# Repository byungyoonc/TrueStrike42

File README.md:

# TrueStrike42

TrueStrike42 is a columnar staggered unibody split Hall-effect keyboard designed to maximize performance[^1] and minimize finger fatigue.

[^1]: specifically on rhythm games

# Layout

# How to build
Refer to the [build guide](doc/buildguide.md) for detailed instructions.

# Firmware
> [!WARNING]
> MCU will behave very erratic (e.g. sending random keypresses rapidly) right after flashing the firmware, before soldering all the components on the board. This is because MCU's analogue pins are connected to nothing, resulting in noise sensor values. 
>
> Disconnect the MCU from the PC as soon as possible after the successful firmware flash to prevent chaos.
> 
## Use Precompiled Binary
Flash `fw/truestrike42_via.uf2` to your RP2040 microcontroller in bootloader mode.

## Build on Your Own
### Option A
Copy the `fw/truestrike42` folder into your cloned QMK Firmware repository's `keyboards` folder, then run `qmk compile -kb truestrike42 -km via`.

### Option B
- [QMK Firmware fork](https://github.com/byungyoonc/qmk_firmware/tree/Truestrike42)
- [VIA QMK Userspace fork](https://github.com/byungyoonc/qmk_userspace_via/tree/truestrike42)

The branches above are from my fork of the QMK Firmware/Userspace repository which supports firmware compilation for TrueStrike42. 

Follow [this guide for External QMK Userspace](https://docs.qmk.fm/newbs_external_userspace) to build it yourself.

# Using VIA HE Configurations
You can access the following tools in VIA by selecting **HE TOOLS** in the menu next to **LIGHTING**.

## Load VIA Definition
Open `fw/truestrike42.json` in VIA's **DESIGN** tab to enable VIA support for TrueStrike42.

## Calibrations
**Make sure to run the calibration at least once before using the keyboard!**
### Bottoming Calibration
Calibrates Hall-effect sensor values for each switch when it is fully bottomed out.

Toggle on, fully bottom out each switch, then toggle off.

### Noise Floor Calibration
Calibrates the ambient magnetic flux fluctuation detected by the Hall-effect sensors.

Click once while leaving the keyboard untouched for a brief period. The firmware samples the noise baseline.

### Show Calibration Data
Prints out current calibration data to the debug console.

### Clear Bottoming Calibration Data
Resets Bottoming Calibration Data to prepare for recalibration. Use this when replacing your Hall-effect switches.

## Actuation
### Mode
Choose between APC and Rapid Trigger.

APC works like a traditional digital switch, but you can change where actuation/release occurs.

Rapid Trigger tracks the switch's height to determine whether the key is being pressed down or released.

### Offsets
Sets the offset values for the selected Mode.

The value ranges from 1 (Topmost) to 255 (Bottommost).

# Related Projects

- [Cipulot's EC Boards](https://github.com/qmk/qmk_firmware/tree/master/keyboards/cipulot/common)
  - TrueStrike42's QMK firmware code for analog signal processing was heavily based on the code for the Cipulot's EC boards.
- [Boardloaf HE](https://github.com/Hanthebot/Boardloaf-HE)
  - 36 key HE split keyboard project by Hanthebot. Their schematics design was derived from TrueStrike42.

# Copyright Notice
`True-Strike-icon.kicad_mod` was created by modifying an icon image for True Strike in the game Baldur's Gate 3, a game by Larian Studios. I used it in accordance with the [Larian Fan Content Policy](https://larian.com/fan-content-policy).

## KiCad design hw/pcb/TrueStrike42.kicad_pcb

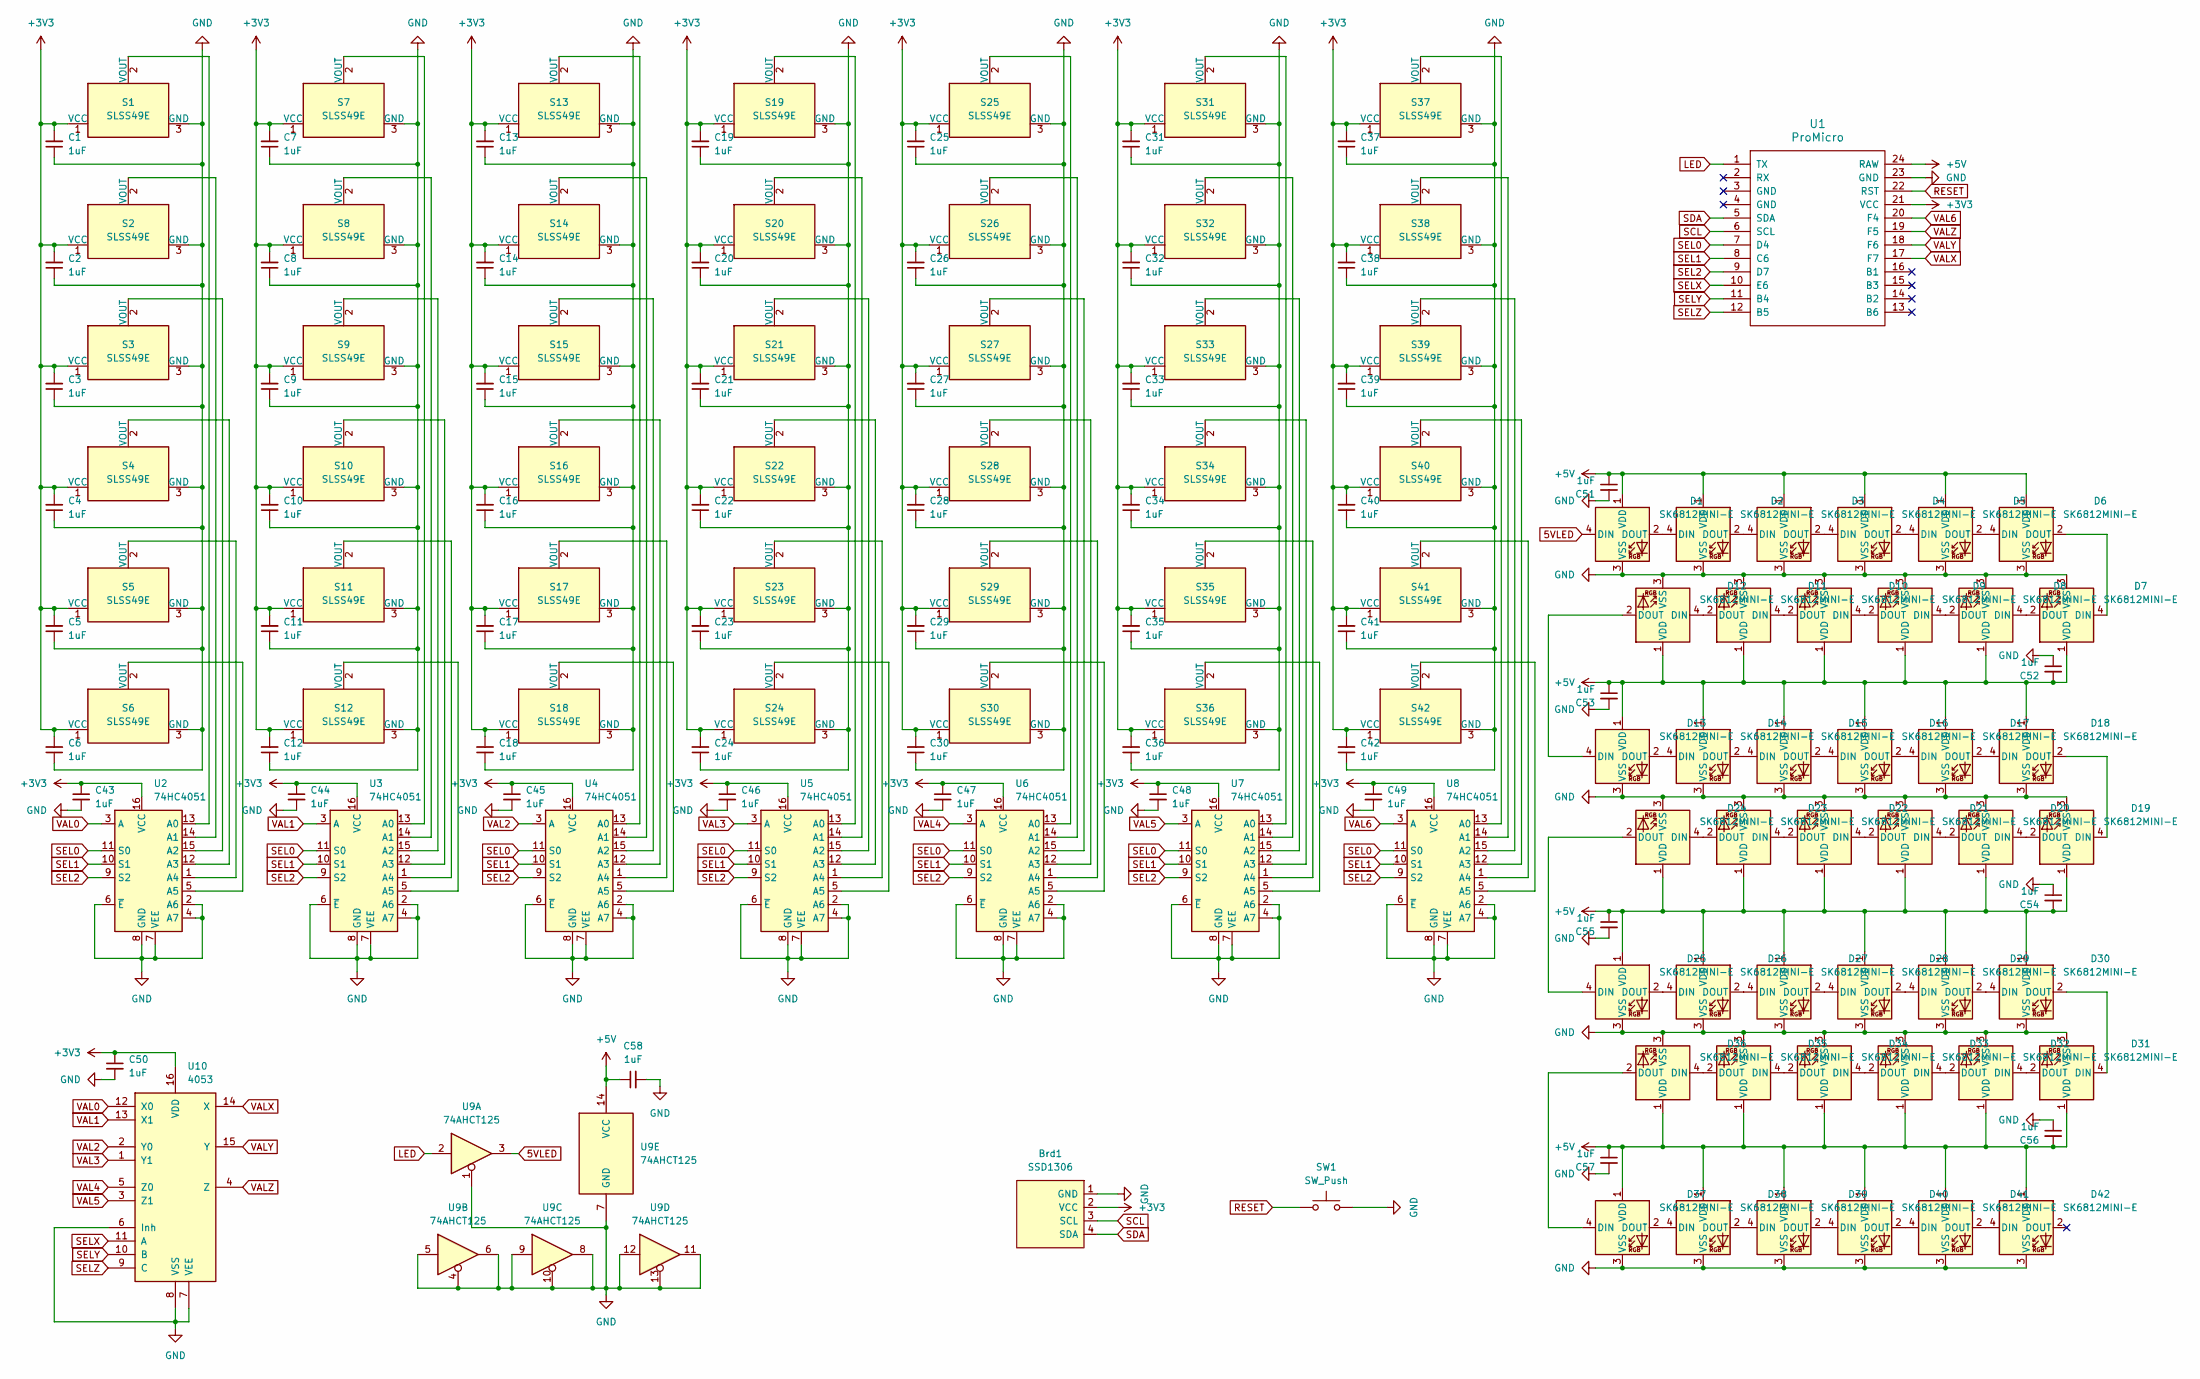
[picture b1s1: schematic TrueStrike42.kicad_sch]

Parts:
Brd1: SSD1306; 128x64OLED
C1, C2, C3, C4, C5, C6, C7, C8, C9, C10, C11, C12, C13, C14, C15, C16, C17, C18, C19, C20, C21, C22, C23, C24, C25, C26, C27, C28, C29, C30, C31, C32, C33, C34, C35, C36, C37, C38, C39, C40, C41, C42, C43, C44, C45, C46, C47, C48, C49, C50, C51, C52, C53, C54, C55, C56, C57, C58: 1uF; C_0805_2012Metric_Pad1.18x1.45mm_HandSolder
D1, D2, D3, D4, D5, D6, D13, D14, D15, D16, D17, D18, D25, D26, D27, D28, D29, D30, D37, D38, D39, D40, D41, D42: SK6812MINI-E; SK6812MINI-E_nusumi
D7, D8, D9, D10, D11, D12, D19, D20, D21, D22, D23, D24, D31, D32, D33, D34, D35, D36: SK6812MINI-E; SK6812MINI-E_nusumi_Rotated
S1, S2, S3, S4, S5, S6, S7, S8, S9, S10, S11, S12, S13, S14, S15, S16, S17, S18, S19, S20, S21, S22, S23, S24, S25, S26, S27, S28, S29, S30, S31, S32, S33, S34, S35, S36, S37, S38, S41, S42: SLSS49E; HE-Switch-1U
S39, S40: SLSS49E; HE-Switch-2U
SW1: SW_Push; SW_Tactile_SPST_NO_Straight_CK_PTS636Sx25SMTRLFS
U1: ProMicro
U2, U3, U4, U5, U6, U7, U8: 74HC4051; SOIC-16_3.9x9.9mm_P1.27mm
U9: 74AHCT125; SOIC-14_3.9x8.7mm_P1.27mm
U10: 4053; SOIC-16_3.9x9.9mm_P1.27mm

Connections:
5VLED: D1.4 (DIN), U9.3
+3V3: Brd1.2 (VCC), C1.2, C2.2, C3.2, C4.2, C5.2, C6.2, C7.2, C8.2, C9.2, C10.2, C11.2, C12.2, C13.2, C14.2, C15.2, C16.2, C17.2, C18.2, C19.2, C20.2, C21.2, C22.2, C23.2, C24.2, C25.2, C26.2, C27.2, C28.2, C29.2, C30.2, C31.2, C32.2, C33.2, C34.2, C35.2, C36.2, C37.2, C38.2, C39.2, C40.2, C41.2, C42.2, C43.1, C44.1, C45.1, C46.1, C47.1, C48.1, C49.1, C50.1, S1.1 (VCC), S2.1 (VCC), S3.1 (VCC), S4.1 (VCC), S5.1 (VCC), S6.1 (VCC), S7.1 (VCC), S8.1 (VCC), S9.1 (VCC), S10.1 (VCC), S11.1 (VCC), S12.1 (VCC), S13.1 (VCC), S14.1 (VCC), S15.1 (VCC), S16.1 (VCC), S17.1 (VCC), S18.1 (VCC), S19.1 (VCC), S20.1 (VCC), S21.1 (VCC), S22.1 (VCC), S23.1 (VCC), S24.1 (VCC), S25.1 (VCC), S26.1 (VCC), S27.1 (VCC), S28.1 (VCC), S29.1 (VCC), S30.1 (VCC), S31.1 (VCC), S32.1 (VCC), S33.1 (VCC), S34.1 (VCC), S35.1 (VCC), S36.1 (VCC), S37.1 (VCC), S38.1 (VCC), S39.1 (VCC), S40.1 (VCC), S41.1 (VCC), S42.1 (VCC), U1.21 (VCC), U2.16 (VCC), U3.16 (VCC), U4.16 (VCC), U5.16 (VCC), U6.16 (VCC), U7.16 (VCC), U8.16 (VCC), U10.16 (VDD)
+5V: C51.1, C52.2, C53.1, C54.2, C55.1, C56.2, C57.1, C58.1, D1.1 (VDD), D2.1 (VDD), D3.1 (VDD), D4.1 (VDD), D5.1 (VDD), D6.1 (VDD), D7.1 (VDD), D8.1 (VDD), D9.1 (VDD), D10.1 (VDD), D11.1 (VDD), D12.1 (VDD), D13.1 (VDD), D14.1 (VDD), D15.1 (VDD), D16.1 (VDD), D17.1 (VDD), D18.1 (VDD), D19.1 (VDD), D20.1 (VDD), D21.1 (VDD), D22.1 (VDD), D23.1 (VDD), D24.1 (VDD), D25.1 (VDD), D26.1 (VDD), D27.1 (VDD), D28.1 (VDD), D29.1 (VDD), D30.1 (VDD), D31.1 (VDD), D32.1 (VDD), D33.1 (VDD), D34.1 (VDD), D35.1 (VDD), D36.1 (VDD), D37.1 (VDD), D38.1 (VDD), D39.1 (VDD), D40.1 (VDD), D41.1 (VDD), D42.1 (VDD), U1.24 (RAW), U9.14 (VCC)
GND: Brd1.1 (GND), C1.1, C2.1, C3.1, C4.1, C5.1, C6.1, C7.1, C8.1, C9.1, C10.1, C11.1, C12.1, C13.1, C14.1, C15.1, C16.1, C17.1, C18.1, C19.1, C20.1, C21.1, C22.1, C23.1, C24.1, C25.1, C26.1, C27.1, C28.1, C29.1, C30.1, C31.1, C32.1, C33.1, C34.1, C35.1, C36.1, C37.1, C38.1, C39.1, C40.1, C41.1, C42.1, C43.2, C44.2, C45.2, C46.2, C47.2, C48.2, C49.2, C50.2, C51.2, C52.1, C53.2, C54.1, C55.2, C56.1, C57.2, C58.2, D1.3 (VSS), D2.3 (VSS), D3.3 (VSS), D4.3 (VSS), D5.3 (VSS), D6.3 (VSS), D7.3 (VSS), D8.3 (VSS), D9.3 (VSS), D10.3 (VSS), D11.3 (VSS), D12.3 (VSS), D13.3 (VSS), D14.3 (VSS), D15.3 (VSS), D16.3 (VSS), D17.3 (VSS), D18.3 (VSS), D19.3 (VSS), D20.3 (VSS), D21.3 (VSS), D22.3 (VSS), D23.3 (VSS), D24.3 (VSS), D25.3 (VSS), D26.3 (VSS), D27.3 (VSS), D28.3 (VSS), D29.3 (VSS), D30.3 (VSS), D31.3 (VSS), D32.3 (VSS), D33.3 (VSS), D34.3 (VSS), D35.3 (VSS), D36.3 (VSS), D37.3 (VSS), D38.3 (VSS), D39.3 (VSS), D40.3 (VSS), D41.3 (VSS), D42.3 (VSS), S1.3 (GND), S2.3 (GND), S3.3 (GND), S4.3 (GND), S5.3 (GND), S6.3 (GND), S7.3 (GND), S8.3 (GND), S9.3 (GND), S10.3 (GND), S11.3 (GND), S12.3 (GND), S13.3 (GND), S14.3 (GND), S15.3 (GND), S16.3 (GND), S17.3 (GND), S18.3 (GND), S19.3 (GND), S20.3 (GND), S21.3 (GND), S22.3 (GND), S23.3 (GND), S24.3 (GND), S25.3 (GND), S26.3 (GND), S27.3 (GND), S28.3 (GND), S29.3 (GND), S30.3 (GND), S31.3 (GND), S32.3 (GND), S33.3 (GND), S34.3 (GND), S35.3 (GND), S36.3 (GND), S37.3 (GND), S38.3 (GND), S39.3 (GND), S40.3 (GND), S41.3 (GND), S42.3 (GND), SW1.2, U1.23 (GND), U2.2 (A6), U2.4 (A7), U2.6 (~E), U2.7 (VEE), U2.8 (GND), U3.2 (A6), U3.4 (A7), U3.6 (~E), U3.7 (VEE), U3.8 (GND), U4.2 (A6), U4.4 (A7), U4.6 (~E), U4.7 (VEE), U4.8 (GND), U5.2 (A6), U5.4 (A7), U5.6 (~E), U5.7 (VEE), U5.8 (GND), U6.2 (A6), U6.4 (A7), U6.6 (~E), U6.7 (VEE), U6.8 (GND), U7.2 (A6), U7.4 (A7), U7.6 (~E), U7.7 (VEE), U7.8 (GND), U8.2 (A6), U8.4 (A7), U8.6 (~E), U8.7 (VEE), U8.8 (GND), U9.1, U9.4, U9.5, U9.6, U9.7 (GND), U9.8, U9.9, U9.10, U9.11, U9.12, U9.13, U10.6 (Inh), U10.7 (VEE), U10.8 (VSS); also elsewhere on the board
LED: U1.1 (TX), U9.2
unnamed: D1.2 (DOUT), D2.4 (DIN)
unnamed: D2.2 (DOUT), D3.4 (DIN)
unnamed: D3.2 (DOUT), D4.4 (DIN)
unnamed: D4.2 (DOUT), D5.4 (DIN)
unnamed: D5.2 (DOUT), D6.4 (DIN)
unnamed: D6.2 (DOUT), D7.4 (DIN)
unnamed: D7.2 (DOUT), D8.4 (DIN)
unnamed: D8.2 (DOUT), D9.4 (DIN)
unnamed: D9.2 (DOUT), D10.4 (DIN)
unnamed: D10.2 (DOUT), D11.4 (DIN)
unnamed: D11.2 (DOUT), D12.4 (DIN)
unnamed: D12.2 (DOUT), D13.4 (DIN)
unnamed: D13.2 (DOUT), D14.4 (DIN)
unnamed: D14.2 (DOUT), D15.4 (DIN)
unnamed: D15.2 (DOUT), D16.4 (DIN)
unnamed: D16.2 (DOUT), D17.4 (DIN)
unnamed: D17.2 (DOUT), D18.4 (DIN)
unnamed: D18.2 (DOUT), D19.4 (DIN)
unnamed: D19.2 (DOUT), D20.4 (DIN)
unnamed: D20.2 (DOUT), D21.4 (DIN)
unnamed: D21.2 (DOUT), D22.4 (DIN)
unnamed: D22.2 (DOUT), D23.4 (DIN)
unnamed: D23.2 (DOUT), D24.4 (DIN)
unnamed: D24.2 (DOUT), D25.4 (DIN)
unnamed: D25.2 (DOUT), D26.4 (DIN)
unnamed: D26.2 (DOUT), D27.4 (DIN)
unnamed: D27.2 (DOUT), D28.4 (DIN)
unnamed: D28.2 (DOUT), D29.4 (DIN)
unnamed: D29.2 (DOUT), D30.4 (DIN)
unnamed: D30.2 (DOUT), D31.4 (DIN)
unnamed: D31.2 (DOUT), D32.4 (DIN)
unnamed: D32.2 (DOUT), D33.4 (DIN)
unnamed: D33.2 (DOUT), D34.4 (DIN)
unnamed: D34.2 (DOUT), D35.4 (DIN)
unnamed: D35.2 (DOUT), D36.4 (DIN)
unnamed: D36.2 (DOUT), D37.4 (DIN)
unnamed: D37.2 (DOUT), D38.4 (DIN)
unnamed: D38.2 (DOUT), D39.4 (DIN)
unnamed: D39.2 (DOUT), D40.4 (DIN)
unnamed: D40.2 (DOUT), D41.4 (DIN)
unnamed: D41.2 (DOUT), D42.4 (DIN)
unnamed: S1.2 (VOUT), U2.13 (A0)
unnamed: S2.2 (VOUT), U2.14 (A1)
unnamed: S3.2 (VOUT), U2.15 (A2)
unnamed: S4.2 (VOUT), U2.12 (A3)
unnamed: S5.2 (VOUT), U2.1 (A4)
unnamed: S6.2 (VOUT), U2.5 (A5)
unnamed: S7.2 (VOUT), U3.13 (A0)
unnamed: S8.2 (VOUT), U3.14 (A1)
unnamed: S9.2 (VOUT), U3.15 (A2)
unnamed: S10.2 (VOUT), U3.12 (A3)
unnamed: S11.2 (VOUT), U3.1 (A4)
unnamed: S12.2 (VOUT), U3.5 (A5)
unnamed: S13.2 (VOUT), U4.13 (A0)
unnamed: S14.2 (VOUT), U4.14 (A1)
unnamed: S15.2 (VOUT), U4.15 (A2)
unnamed: S16.2 (VOUT), U4.12 (A3)
unnamed: S17.2 (VOUT), U4.1 (A4)
unnamed: S18.2 (VOUT), U4.5 (A5)
unnamed: S19.2 (VOUT), U5.13 (A0)
unnamed: S20.2 (VOUT), U5.14 (A1)
unnamed: S21.2 (VOUT), U5.15 (A2)
unnamed: S22.2 (VOUT), U5.12 (A3)
unnamed: S23.2 (VOUT), U5.1 (A4)
unnamed: S24.2 (VOUT), U5.5 (A5)
unnamed: S25.2 (VOUT), U6.13 (A0)
unnamed: S26.2 (VOUT), U6.14 (A1)
unnamed: S27.2 (VOUT), U6.15 (A2)
unnamed: S28.2 (VOUT), U6.12 (A3)
unnamed: S29.2 (VOUT), U6.1 (A4)
unnamed: S30.2 (VOUT), U6.5 (A5)
unnamed: S31.2 (VOUT), U7.13 (A0)
unnamed: S32.2 (VOUT), U7.14 (A1)
unnamed: S33.2 (VOUT), U7.15 (A2)
unnamed: S34.2 (VOUT), U7.12 (A3)
unnamed: S35.2 (VOUT), U7.1 (A4)
unnamed: S36.2 (VOUT), U7.5 (A5)
unnamed: S37.2 (VOUT), U8.13 (A0)
unnamed: S38.2 (VOUT), U8.14 (A1)
unnamed: S39.2 (VOUT), U8.15 (A2)
unnamed: S40.2 (VOUT), U8.12 (A3)
unnamed: S41.2 (VOUT), U8.1 (A4)
unnamed: S42.2 (VOUT), U8.5 (A5)
RESET: SW1.1, U1.22 (RST); also elsewhere on the board
SCL: Brd1.3 (SCL), U1.6 (SCL)
SDA: Brd1.4 (SDA), U1.5 (SDA)
SEL0: U1.7 (D4), U2.11 (S0), U3.11 (S0), U4.11 (S0), U5.11 (S0), U6.11 (S0), U7.11 (S0), U8.11 (S0)
SEL1: U1.8 (C6), U2.10 (S1), U3.10 (S1), U4.10 (S1), U5.10 (S1), U6.10 (S1), U7.10 (S1), U8.10 (S1)
SEL2: U1.9 (D7), U2.9 (S2), U3.9 (S2), U4.9 (S2), U5.9 (S2), U6.9 (S2), U7.9 (S2), U8.9 (S2)
SELX: U1.10 (E6), U10.11 (A)
SELY: U1.11 (B4), U10.10 (B)
SELZ: U1.12 (B5), U10.9 (C)
VAL0: U2.3 (A), U10.12 (X0)
VAL1: U3.3 (A), U10.13 (X1)
VAL2: U4.3 (A), U10.2 (Y0)
VAL3: U5.3 (A), U10.1 (Y1)
VAL4: U6.3 (A), U10.5 (Z0)
VAL5: U7.3 (A), U10.3 (Z1)
VAL6: U1.20 (F4), U8.3 (A)
VALX: U1.17 (F7), U10.14 (X)
VALY: U1.18 (F6), U10.15 (Y)
VALZ: U1.19 (F5), U10.4 (Z)

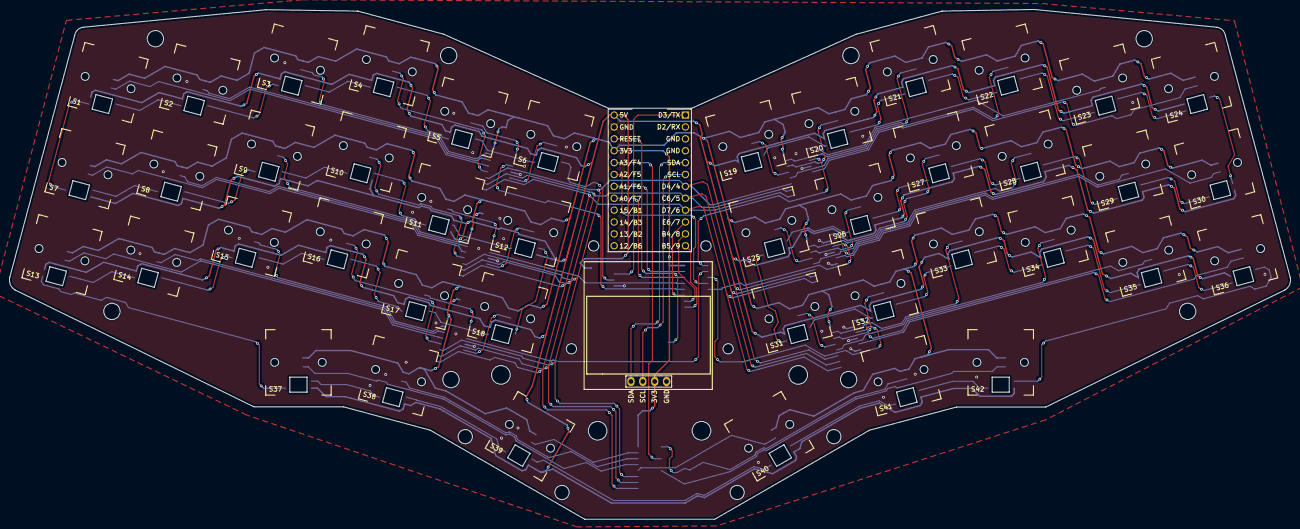
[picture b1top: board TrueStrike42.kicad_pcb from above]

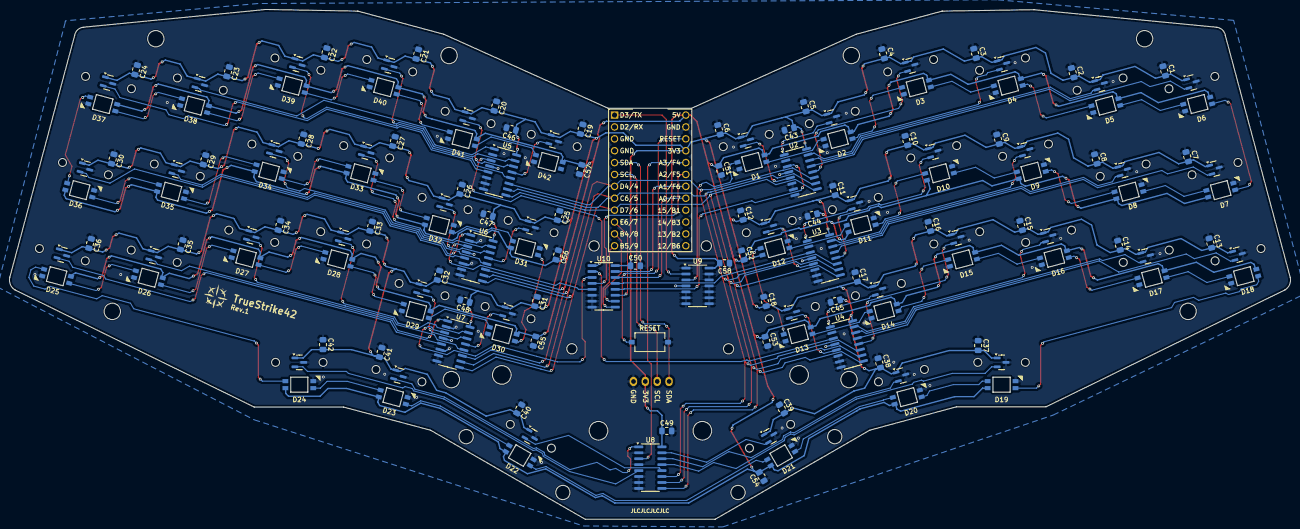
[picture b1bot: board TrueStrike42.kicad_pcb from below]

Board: 2 copper layers, 273.9 x 109.0 mm, 154 parts (111 on the bottom side), 107 nets.

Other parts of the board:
RESET: SW_Push; SW_Tactile_SPST_NO_Straight_CK_PTS636Sx25SMTRLFS

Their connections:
GND: RESET.2; also elsewhere on the board
RESET: RESET.1; also elsewhere on the board

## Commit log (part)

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2024-06-23 Initialize KiCad project
2024-06-23 Add submodules for symbols and footprints
2024-06-23 Add symbols/footprints
2024-07-10 Add project specific symbol library
    And a symbol for a Hall effect sensor we will use here
2024-07-10 Add ProMicro symbols and footprint
2024-07-14 Schema v1
2024-07-15 Add footprints for HE switch
2024-07-15 PCB layout v1
2024-07-16 Add vertical versions of >1u HE switch footprints
2024-07-20 Add a submodule for symbols and footprints
2024-07-21 Update TrueStrike42.kicad_sch
    Add LED matrix schematics
2024-07-26 Add SK6812MINI-E footprints
2024-07-26 Update PCB and schematic
2024-07-26 Update TrueStrike42.kicad_pcb
    Rotate left/right hand clusters
2024-07-26 Update TrueStrike42.kicad_pcb
    Finalize board silhouette
2024-07-26 Update TrueStrike42.kicad_pro
    Add PWR net class
2024-07-27 Update TrueStrike42.kicad_sch
    Remove unnecessary capacitors
2024-07-27 Update TrueStrike42.kicad_pcb
    Tracing work in progress
2024-08-03 Update TrueStrike42.kicad_pcb
    Wiring wip: right side done
2024-08-11 Update TrueStrike42.kicad_pcb
    Wiring finished except for GND
2024-08-12 Update TrueStrike42.kicad_pcb
    Finished routing
2024-08-12 Add submodule for SSD1306
2024-08-12 Add SSD1306 to footprint and symbol libraries
2024-08-12 Add LED screen and a reset switch
2024-08-12 GND fill + DRC check pass
2024-08-14 Update functional silkscreens
2024-08-14 Update TrueStrike42.kicad_pcb
    Add mounting holes
2024-08-14 Add logo, fixed wrong pinouts for sensors
2024-08-14 Update reset button label
2024-08-14 Add order number locator for JLCPCB
2024-08-14 Update settings for gerber export
2024-08-14 Generate gerber files
2024-08-15 Refined mounting hole positions to be symmetric
2024-08-15 Update TrueStrike42.kicad_pcb
    Make the rest of the PCB to be symmetric
2024-08-15 Add top plate
2024-08-16 Add OLED/MCU cover
2024-08-16 Add bottom plate
2024-08-16 Update TrueStrike42-top-plate.kicad_pcb
    Change ID location on top plate
2024-08-16 Update TrueStrike42-cover.kicad_pcb
    Add ID location for cover
2024-08-16 Update Gerber output formats
2024-08-16 Update Gerber output format
2024-08-16 Add Gerber outputs
2025-07-20 Add exported Gerber files to .gitignore
2025-07-20 Add a photo of a built TrueStrike42 keyboard
2025-12-22 Upload firmware code and precompiled artifact
2025-12-22 Update README.md to include keyboard layout, firmware guide, VIA usage guide.
2025-12-23 Grammar fix on README
2025-12-23 More grammar fixes on README
2025-12-26 Add the build guide
2025-12-26 Update built keyboard photo with a bit clearer one
2025-12-26 Add missing 0 on number layer on initial keymaps
2025-12-26 Update README to include the picture of the keyboard
2025-12-26 KLE layout diagram was wrong. Uploading the correct one
2025-12-27 Update firmware file and code to correctly enable VIA
2025-12-27 Add notes and warnings about flashing the firmware
